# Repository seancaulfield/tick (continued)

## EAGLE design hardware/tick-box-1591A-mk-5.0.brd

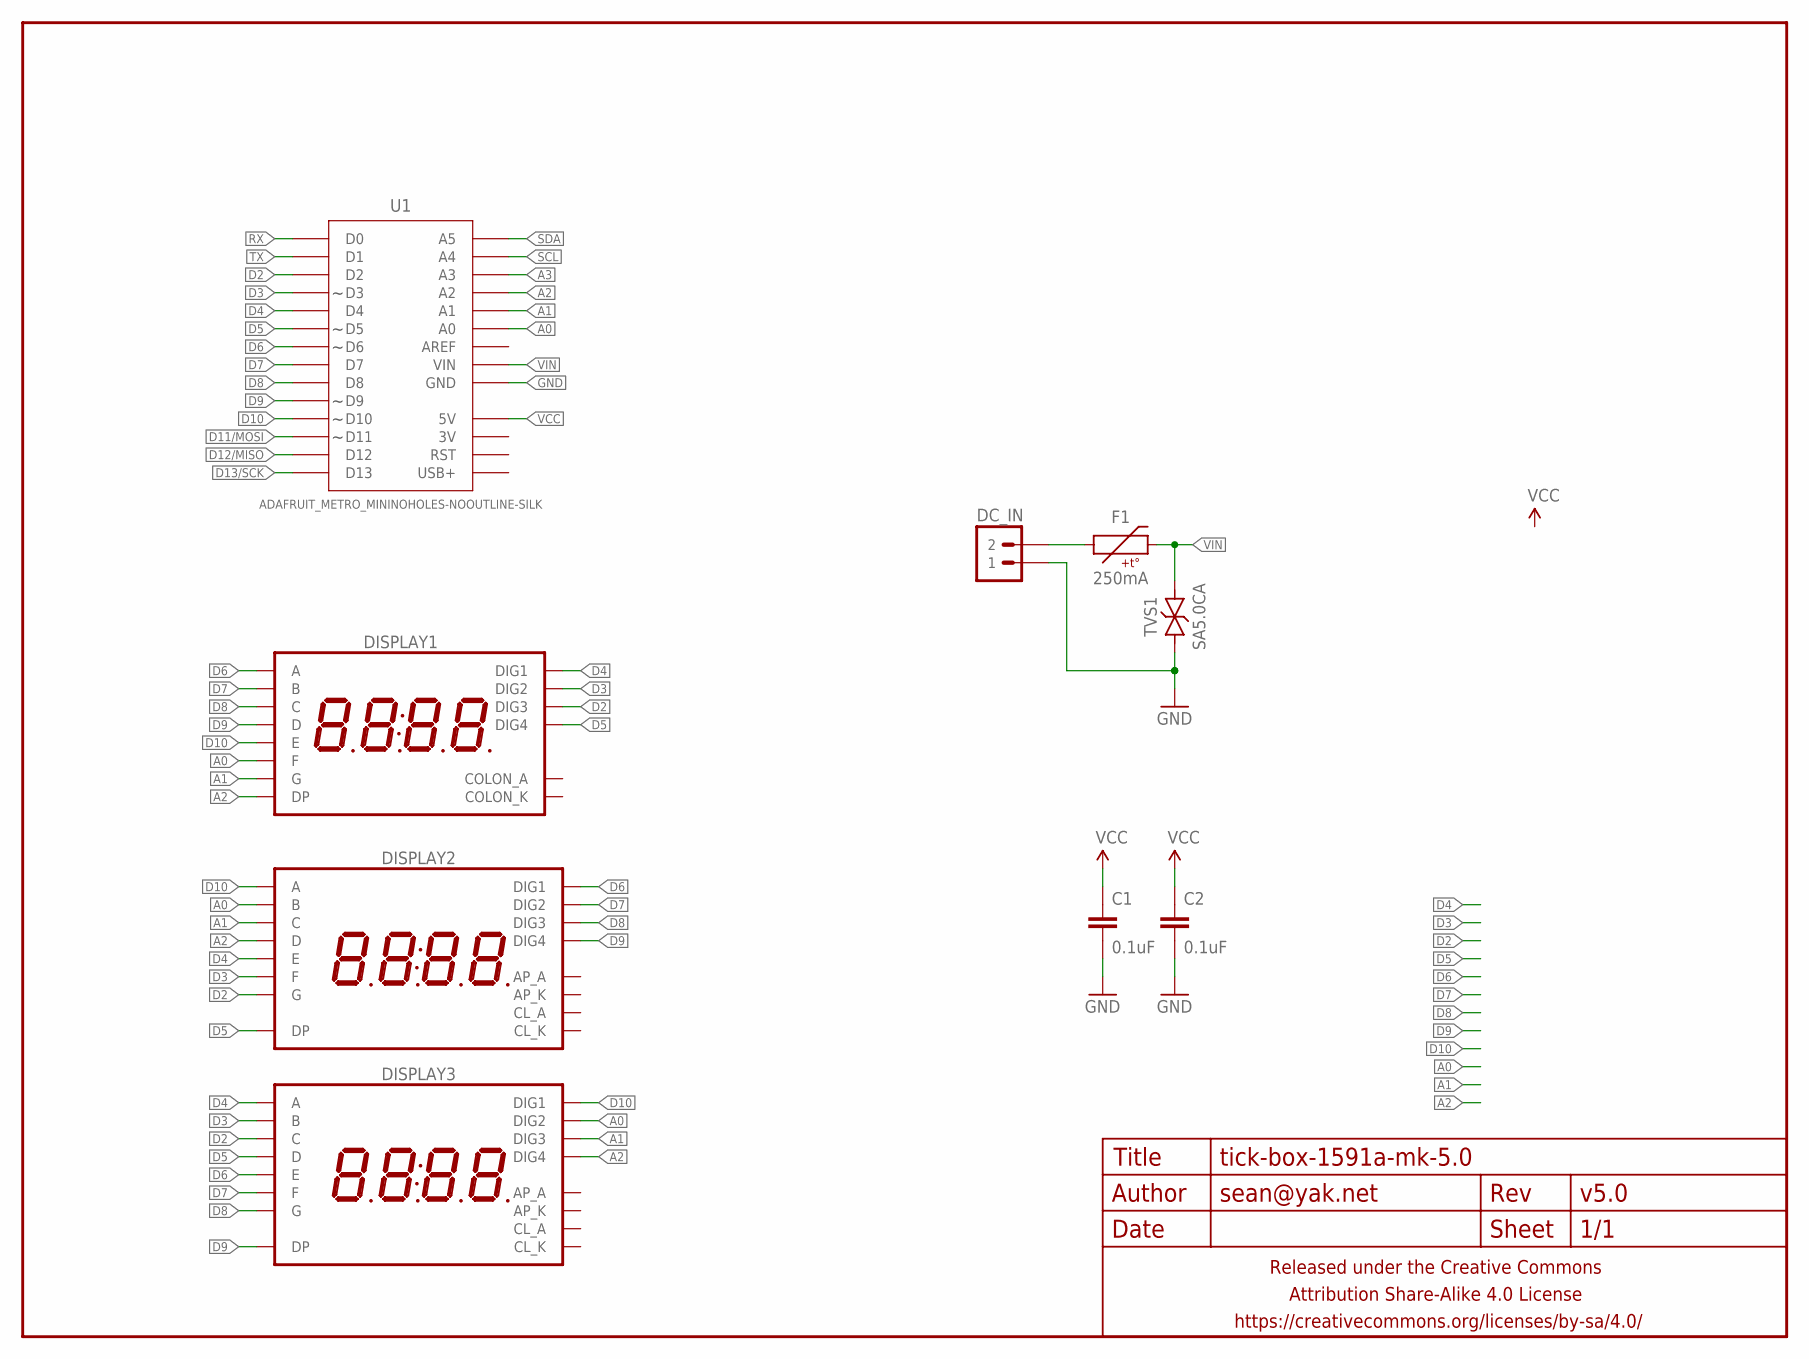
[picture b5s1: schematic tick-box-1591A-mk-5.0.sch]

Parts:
C1, C2: 0.1uF; C0603
DC_IN: M02PTH-CENTERED-R+; 1X02-CENTER-R+
DISPLAY1: 7SEG_4DIGIT_COLON14.2MM-CC-NS; 7SEG_4DIG_NS
DISPLAY2, DISPLAY3: 7SEG_4DIGIT_COLON_APOS; 7SEG_4DIG_10MM
F1: 250mA; PTC-1210
FRAME1: FRAME-LETTERNO_PACKAGE; DUMMY
TVS1: SA5.0CA; SMA-DIODE-TVS-BIDIR
U1: ADAFRUIT_METRO_MININOHOLES-NOOUTLINE-SILK; ADAFRUIT_METRO_MINI

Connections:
A0: DISPLAY1.P$12 (F), DISPLAY2.16 (B), DISPLAY3.2 (DIG2), U1.23 (A0)
A1: DISPLAY1.P$5 (G), DISPLAY2.13 (C), DISPLAY3.6 (DIG3), U1.24 (A1)
A2: DISPLAY1.P$3 (DP), DISPLAY2.3 (D), DISPLAY3.8 (DIG4), U1.25 (A2)
A3: U1.26 (A3)
D2: DISPLAY1.P$10 (DIG3), DISPLAY2.15 (G), DISPLAY3.13 (C), U1.3 (D2)
D3: DISPLAY1.P$11 (DIG2), DISPLAY2.11 (F), DISPLAY3.16 (B), U1.4 (D3)
D4: DISPLAY1.P$14 (DIG1), DISPLAY2.5 (E), DISPLAY3.14 (A), U1.5 (D4)
D5: DISPLAY1.P$6 (DIG4), DISPLAY2.7 (DP), DISPLAY3.3 (D), U1.6 (D5)
D6: DISPLAY1.P$13 (A), DISPLAY2.1 (DIG1), DISPLAY3.5 (E), U1.7 (D6)
D7: DISPLAY1.P$9 (B), DISPLAY2.2 (DIG2), DISPLAY3.11 (F), U1.8 (D7)
D8: DISPLAY1.P$4 (C), DISPLAY2.6 (DIG3), DISPLAY3.15 (G), U1.9 (D8)
D9: DISPLAY1.P$2 (D), DISPLAY2.8 (DIG4), DISPLAY3.7 (DP), U1.10 (D9)
D10: DISPLAY1.P$1 (E), DISPLAY2.14 (A), DISPLAY3.1 (DIG1), U1.11 (D10)
D11/MOSI: U1.12 (D11)
D12/MISO: U1.13 (D12)
D13/SCK: U1.14 (D13)
GND: C1.2, C2.2, DC_IN.1, TVS1.1, U1.19 (GND), U1.20 (GND)
unnamed: DC_IN.2, F1.1
RX: U1.1 (D0)
SCL: U1.27 (A4)
SDA: U1.28 (A5)
TX: U1.2 (D1)
VCC: C1.1, C2.1, U1.18 (5V)
VIN: F1.2, TVS1.2, U1.21 (VIN)

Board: 2 copper layers, 10 parts (3 on the bottom side), 16 nets, no tracks yet.
